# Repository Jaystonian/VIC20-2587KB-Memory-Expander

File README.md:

# VIC20-2587KB-Memory-Expander
An REU for the Commodore VIC-20 with 512KB reprogrammable Flash memory, 35KB RAM Expansion and 2MB paged memory in 8KB blocks

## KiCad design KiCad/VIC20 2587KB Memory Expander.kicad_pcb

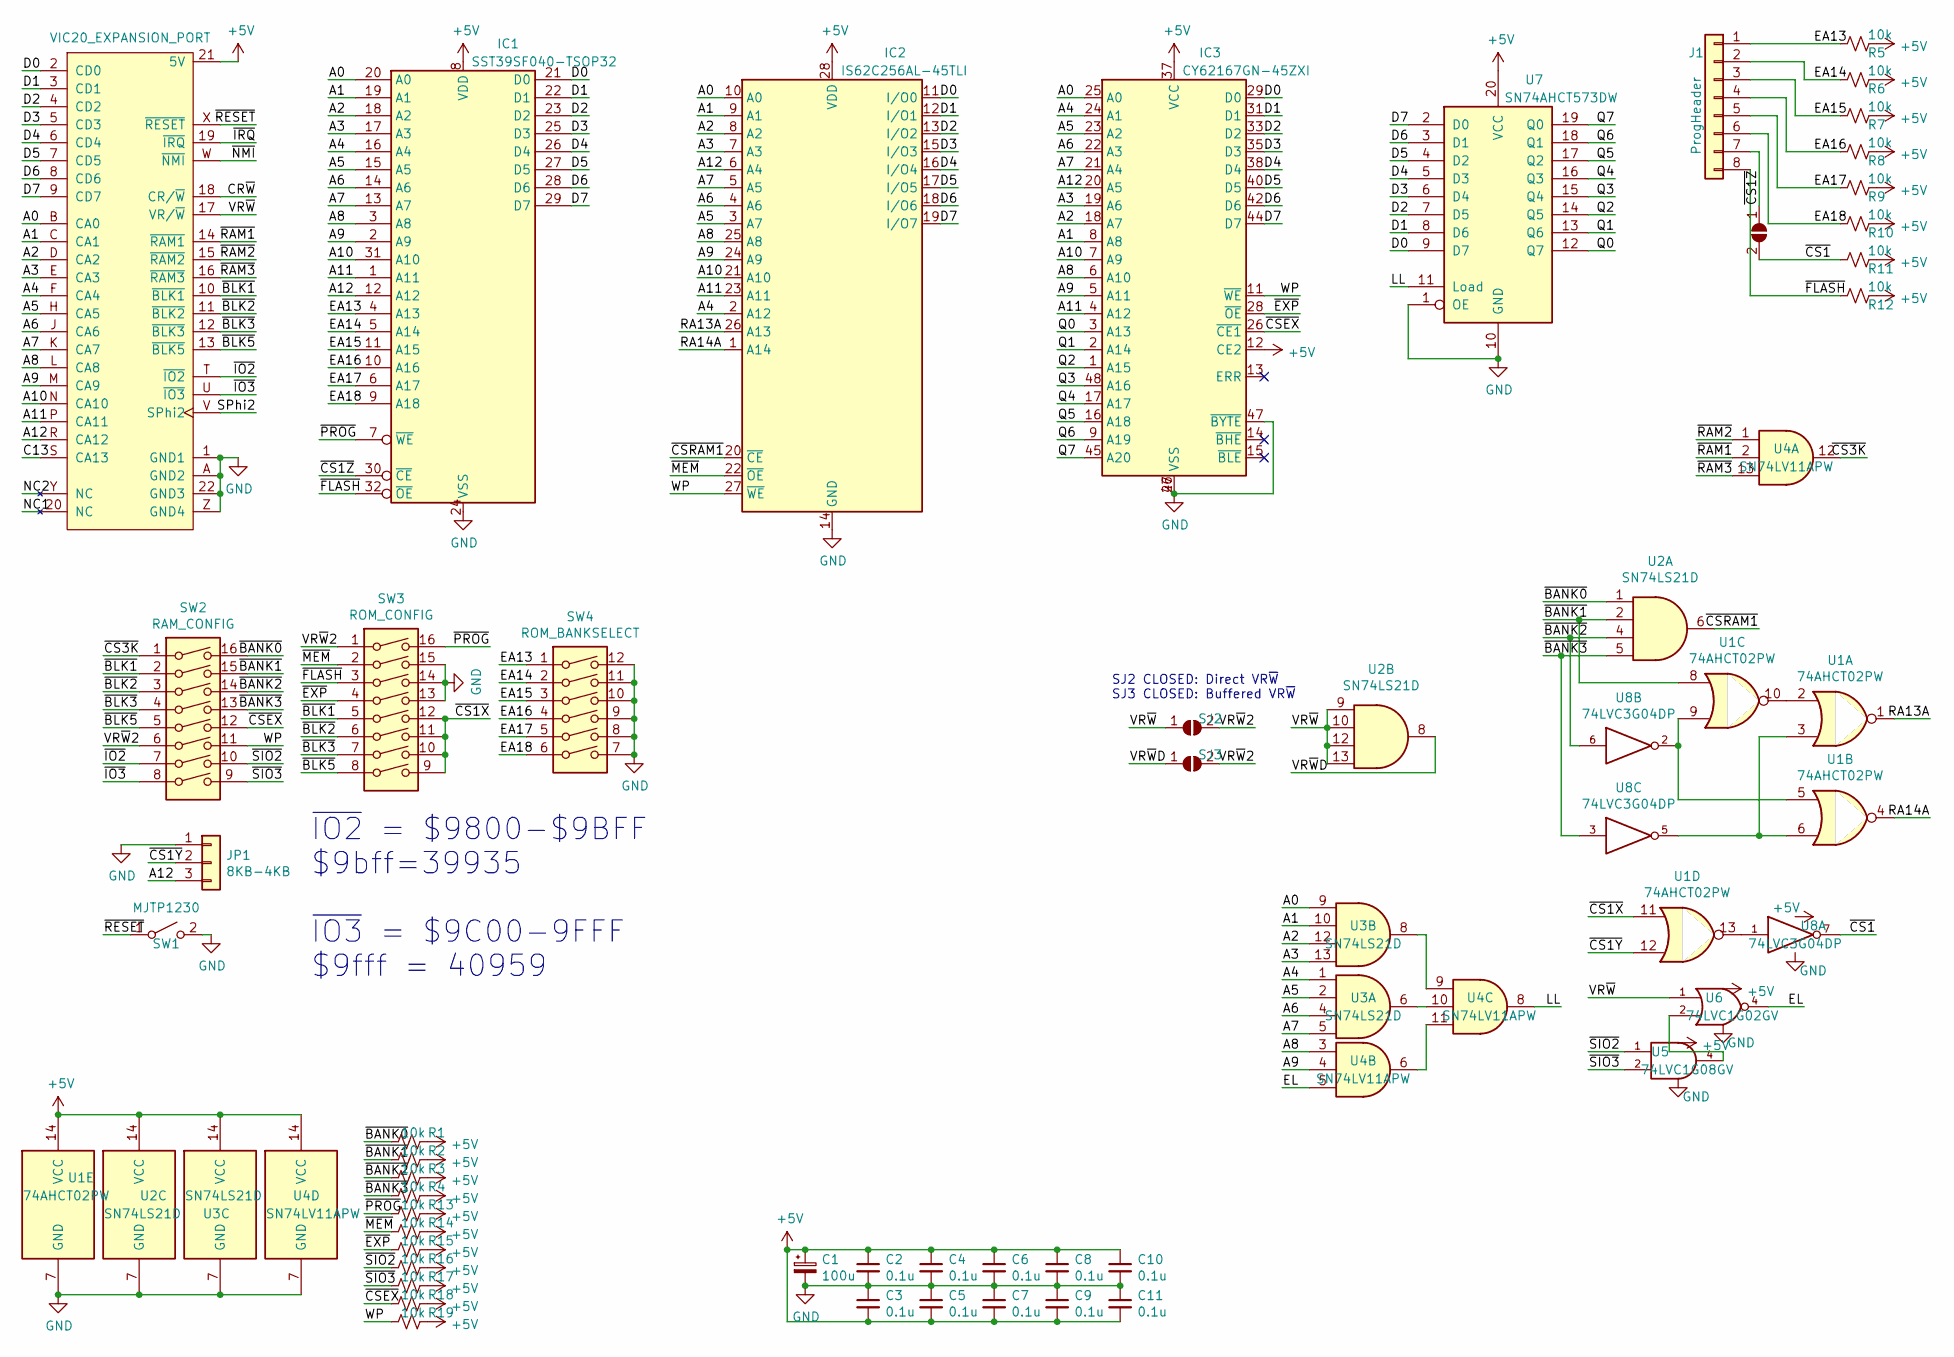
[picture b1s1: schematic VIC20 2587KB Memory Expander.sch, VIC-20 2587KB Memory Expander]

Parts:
C1: 100u; CP_Radial_D8.0mm_P3.50mm
C2, C3, C4, C5, C6, C7, C8, C9, C10, C11: 0.1u; C_0603_1608Metric_Pad1.05x0.95mm_HandSolder
IC1: SST39SF040-TSOP32; TSOP-32_14x8mm_P0.5mm
IC2: IS62C256AL-45TLI
IC3: CY62167GN-45ZXI; TSOP-I-48_18.4x12mm_P0.5mm
J1: ProgHeader; PinSocket_1x08_P2.54mm_Vertical
JP1: 8KB-4KB; PinHeader_1x03_P2.54mm_Vertical
R1, R2, R3, R4, R5, R6, R7, R8, R9, R10, R11, R12, R13, R14, R15, R16, R17, R18, R19: 10k; R_0805_2012Metric_Pad1.15x1.40mm_HandSolder
SJ1, SJ2, SJ3: SolderJumper_2_Open; SolderJumper-2_P1.3mm_Open_TrianglePad1.0x1.5mm
SW1: MJTP1230; SW_PUSH_6mm_H8mm
SW2: RAM_CONFIG; SW_DIP_SPSTx08_Slide_9.78x22.5mm_W7.62mm_P2.54mm
SW3: ROM_CONFIG; SW_DIP_SPSTx08_Slide_9.78x22.5mm_W7.62mm_P2.54mm
SW4: ROM_BANKSELECT; SW_DIP_SPSTx06_Slide_9.78x17.42mm_W7.62mm_P2.54mm
U1: 74AHCT02PW; TSSOP-14_4.4x5mm_P0.65mm
U2, U3: SN74LS21D; SOIC-14_3.9x8.7mm_P1.27mm
U4: SN74LV11APW; TSSOP-14_4.4x5mm_P0.65mm
U5: 74LVC1G08GV; SOT-753
U6: 74LVC1G02GV; SOT-753
U7: SN74AHCT573DW; SOIC-20W_7.5x12.8mm_P1.27mm
U8: 74LVC3G04DP; TSSOP-8_3x3mm_P0.65mm
X1: VIC20_EXPANSION_PORT; VIC20_EXPANSION_CARD_sven

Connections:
+5V: C1.1, C2.1, C3.2, C4.1, C5.2, C6.1, C7.2, C8.1, C9.2, C10.1, C11.2, IC1.8 (VDD), IC2.28 (VDD), IC3.12 (CE2), IC3.37 (VCC), R1.1, R2.1, R3.1, R4.1, R5.1, R6.1, R7.1, R8.1, R9.1, R10.1, R11.1, R12.1, R13.1, R14.1, R15.1, R16.1, R17.1, R18.1, R19.1, U1.14 (VCC), U2.14 (VCC), U3.14 (VCC), U4.14 (VCC), U5.5 (VCC), U6.5 (VCC), U7.20 (VCC), U8.8 (VCC), X1.21 (5V)
/A0: IC1.20 (A0), IC2.10 (A0), IC3.25 (A0), U3.9, X1.B (CA0)
/A1: IC1.19 (A1), IC2.9 (A1), IC3.8 (A8), U3.10, X1.C (CA1)
/A2: IC1.18 (A2), IC2.8 (A2), IC3.18 (A7), U3.12, X1.D (CA2)
/A3: IC1.17 (A3), IC2.7 (A3), IC3.19 (A6), U3.13, X1.E (CA3)
/A4: IC1.16 (A4), IC2.2 (A12), IC3.24 (A1), U3.1, X1.F (CA4)
/A5: IC1.15 (A5), IC2.3 (A7), IC3.23 (A2), U3.2, X1.H (CA5)
/A6: IC1.14 (A6), IC2.4 (A6), IC3.22 (A3), U3.4, X1.J (CA6)
/A7: IC1.13 (A7), IC2.5 (A5), IC3.21 (A4), U3.5, X1.K (CA7)
/A8: IC1.3 (A8), IC2.25 (A8), IC3.6 (A10), U4.3, X1.L (CA8)
/A9: IC1.2 (A9), IC2.24 (A9), IC3.5 (A11), U4.4, X1.M (CA9)
/A10: IC1.31 (A10), IC2.21 (A10), IC3.7 (A9), X1.N (CA10)
/A11: IC1.1 (A11), IC2.23 (A11), IC3.4 (A12), X1.P (CA11)
/A12: IC1.12 (A12), IC2.6 (A4), IC3.20 (A5), JP1.3, X1.R (CA12)
/C13: X1.S (CA13)
/CR~W: X1.18 (CR/~W~)
/D0: IC1.21 (D0), IC2.11 (I/O0), IC3.29 (D0), U7.9 (D7), X1.2 (CD0)
/D1: IC1.22 (D1), IC2.12 (I/O1), IC3.31 (D1), U7.8 (D6), X1.3 (CD1)
/D2: IC1.23 (D2), IC2.13 (I/O2), IC3.33 (D2), U7.7 (D5), X1.4 (CD2)
/D3: IC1.25 (D3), IC2.15 (I/O3), IC3.35 (D3), U7.6 (D4), X1.5 (CD3)
/D4: IC1.26 (D4), IC2.16 (I/O4), IC3.38 (D4), U7.5 (D3), X1.6 (CD4)
/D5: IC1.27 (D5), IC2.17 (I/O5), IC3.40 (D5), U7.4 (D2), X1.7 (CD5)
/D6: IC1.28 (D6), IC2.18 (I/O6), IC3.42 (D6), U7.3 (D1), X1.8 (CD6)
/D7: IC1.29 (D7), IC2.19 (I/O7), IC3.44 (D7), U7.2 (D0), X1.9 (CD7)
/EA13: IC1.4 (A13), J1.1, R5.2, SW4.1
/EA14: IC1.5 (A14), J1.2, R6.2, SW4.2
/EA15: IC1.11 (A15), J1.3, R7.2, SW4.3
/EA16: IC1.10 (A16), J1.4, R8.2, SW4.4
/EA17: IC1.6 (A17), J1.5, R9.2, SW4.5
/EA18: IC1.9 (A18), J1.6, R10.2, SW4.6
/EL: U4.5, U6.4
/LL: U4.8, U7.11 (Load)
/NC1: X1.20 (NC)
/NC2: X1.Y (NC)
/Q0: IC3.3 (A13), U7.12 (Q7)
/Q1: IC3.2 (A14), U7.13 (Q6)
/Q2: IC3.1 (A15), U7.14 (Q5)
/Q3: IC3.48 (A16), U7.15 (Q4)
/Q4: IC3.17 (A17), U7.16 (Q3)
/Q5: IC3.16 (A18), U7.17 (Q2)
/Q6: IC3.9 (A19), U7.18 (Q1)
/Q7: IC3.45 (A20), U7.19 (Q0)
/RA13A: IC2.26 (A13), U1.1
/RA14A: IC2.1 (A14), U1.4
/SPhi2: X1.V (SPhi2)
/VR~W: SJ2.1 (A), U2.9, U2.10, U2.12, U2.13, U6.1, X1.17 (VR/~W~)
/VR~W~2: SJ2.2 (B), SJ3.2 (B), SW2.6, SW3.1
/VR~W~D: SJ3.1 (A), U2.8
/WP: IC2.27 (~WE), IC3.11 (~WE~), R19.2, SW2.11
/~BANK0: R1.2, SW2.16, U2.1
/~BANK1: R2.2, SW2.15, U1.8, U2.2
/~BANK2: R3.2, SW2.14, U2.4, U8.6
/~BANK3: R4.2, SW2.13, U2.5, U8.3
/~BLK1: SW2.2, SW3.5, X1.10 (~BLK1~)
/~BLK2: SW2.3, SW3.6, X1.11 (~BLK2~)
/~BLK3: SW2.4, SW3.7, X1.12 (~BLK3~)
/~BLK5: SW2.5, SW3.8, X1.13 (~BLK5~)
/~CS1: R11.2, SJ1.2 (B), U8.7
/~CS1X: SW3.9, SW3.10, SW3.11, SW3.12, U1.11
/~CS1Y: JP1.2, U1.12
/~CS1Z: IC1.30 (~CE), J1.7, SJ1.1 (A)
/~CS3K: SW2.1, U4.12
/~CSEX: IC3.26 (~CE1~), R18.2, SW2.12
/~CSRAM1: IC2.20 (~CE), U2.6
/~EXP: IC3.28 (~OE~), R15.2, SW3.4
/~FLASH: IC1.32 (~OE), J1.8, R12.2, SW3.3
/~IO2: SW2.7, X1.T (~IO2)
/~IO3: SW2.8, X1.U (~IO3)
/~IRQ: X1.19 (~IRQ~)
/~MEM: IC2.22 (~OE), R14.2, SW3.2
/~NMI: X1.W (~NMI~)
/~PROG: IC1.7 (~WE), R13.2, SW3.16
/~RAM1: U4.2, X1.14 (~RAM1~)
/~RAM2: U4.1, X1.15 (~RAM2~)
/~RAM3: U4.13, X1.16 (~RAM3~)
/~RESET: SW1.1 (A), X1.X (~RESET~)
/~SIO2: R16.2, SW2.10, U5.1
/~SIO3: R17.2, SW2.9, U5.2
GND: C1.2, C2.2, C3.1, C4.2, C5.1, C6.2, C7.1, C8.2, C9.1, C10.2, C11.1, IC1.24 (VSS), IC2.14 (GND), IC3.27 (VSS), IC3.46 (VSS), IC3.47 (~BYTE), JP1.1, SW1.2 (B), SW3.13, SW3.14, SW3.15, SW4.7, SW4.8, SW4.9, SW4.10, SW4.11, SW4.12, U1.7 (GND), U2.7 (GND), U3.7 (GND), U4.7 (GND), U5.3 (GND), U6.3 (GND), U7.1 (OE), U7.10 (GND), U8.4 (GND), X1.1 (GND1), X1.22 (GND3), X1.A (GND2), X1.Z (GND4)
unnamed: U1.3, U1.6, U8.5
unnamed: U1.5, U1.9, U8.2
unnamed: U1.2, U1.10
unnamed: U1.13, U8.1
unnamed: U3.6, U4.10
unnamed: U3.8, U4.9
unnamed: U4.6, U4.11
unnamed: U5.4, U6.2

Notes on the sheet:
~IO2~ = $9800-$9BFF $9bff=39935 ~IO3~ = $9C00-9FFF $9fff = 40959
SJ2 CLOSED: Direct VR~W~ SJ3 CLOSED: Buffered VR~W~

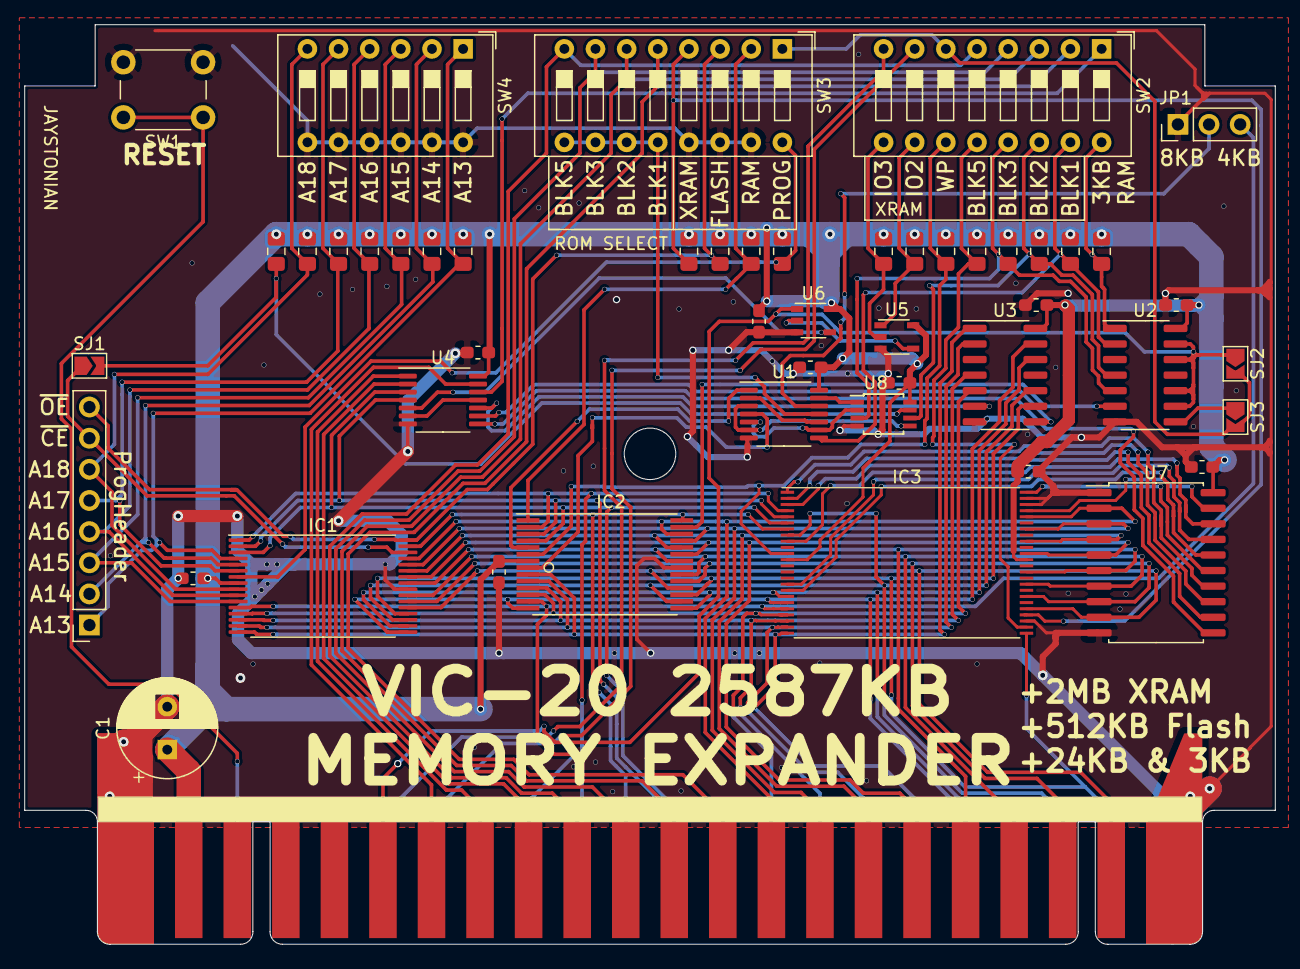
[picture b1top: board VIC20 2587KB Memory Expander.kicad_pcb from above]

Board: 2 copper layers, 102.0 x 75.0 mm, 51 parts (0 on the bottom side), 80 nets.
